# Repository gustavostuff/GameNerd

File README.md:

> **Status:** Active work has shifted to **[Retr01 Nano](nano/README.md)**, a smaller, simpler sibling meant to ship first. The full Retr01 design below is paused for now. It remains the long-term target once Nano is solid.

Retr01 is an MCU-assisted 8-bit system, complemented by a software toolchain. The software consists of 3 different (WIP) packages:

- **Retr01 Studio**: the game editor. Draw maps, tiles, and sprites, then hit **Play** to try your game (uses the emulator render code).
- **Retr01 Emu**: the standalone game player. Runs a cartridge image on your computer. Studio Play uses this same engine.
- **Retr01 Sim**: the board simulator. Shows the ICs and wiring of the motherboard so we can bring up the real design before hardware.

This is the overall hardware roadmap:

- **Retr01-A and Retr01-C** (Arcade and Console): One THT board for both shells. Same **23-IC** core, [**36-pin cart**](docs/cart.md), **RGBS + composite**, 5 V barrel. Arcade microswitch headers **and** PCB footprints for **2x Switchcraft 35RAPC** TRS ([`docs/controllers.md`](docs/controllers.md)).
- **Retr01-H (stage 2)**: Handheld. SMD, battery, LCD + driver, contact pads. Same software contract. It will also include 3.5mm ports for controllers and possibly one more for mono audio + composite.

## Apps

`./build-all` builds Release **Studio**, **Emu**, **Sim**, **Nano Studio**, **Nano Emu**, and **Nano Sim** into `bin/`. `./studio`, `./emu`, and `./sim` (at root) run the full Retr01 binaries. `./unit-tests` runs their test suites.

**Retr01 Nano** (design + apps under [`nano/`](nano/README.md)): `./nano_studio` (optional project path), `./nano_emu [cart.r01nano]`, and `./nano_sim [cart.r01nano]`.

## Main specs

| Aspect | Description |
|--|--|
| CPU | W65C02S @ **8 MHz** |
| Playfield | **128 x 120** of logical resolution (**16 x 15** tiles), board **2x** to **256 x 240** RGBS field |
| Art | **8 x 8** tiles, **2 bpp**, **64** master colors on-board Color PROM IC |
| Worlds | up to **8** worlds x **48** screens each (384-screen "real state"). All within a 512KB cartridge |
| Scroll | **2 x 2** live nametable window + **true second BG** (SNES-like parallax via color-0 show-through) |
| Sprites | **128** OAM entries, **16** per scanline |
| VRAM / RAM | **32 KB** interleaved VRAM + **32 KB** system RAM |

In cartridge, same **32 KB PRG** as classic NES NROM games (Exitebike, Balloon Fight, Ice Climbers) but it buys far more game: **4.5x** more CPU cycles per frame at **8 MHz**, **32 KB** system RAM (not 2 KB). Scroll, sprite line fill and world map streaming are hardware jobs, so PRG stays game logic, not VBlank nametable tricks. A structured **BG0** far plane scrolls under BG1 (color **0** windows) for real dual-layer parallax, not a mapper hack. See [`docs/selling_points.md`](docs/selling_points.md).

## Screenshots

Peek at Retr01 Studio:

Emulator:

Sim:

Main PCB - preliminary design, not tested:

Cart PCB - preliminary design, not tested:

## Where to go next

- [`docs/graphics.md`](docs/graphics.md): VRAM, BG0/BG1, sprites, palettes, graphics ports
- [`docs/selling_points.md`](docs/selling_points.md): NES vs Retr01, including **SNES-like parallax (BG0)**
- [`docs/memory.md`](docs/memory.md): chips, cart layout, read/write timing
- [`docs/hardware.md`](docs/hardware.md): IC BOM, block diagram, bring-up (chips only)
- [`docs/cart.md`](docs/cart.md): cartridge pinout, form factor, USB-C flasher
- [`docs/controllers.md`](docs/controllers.md): Retr01-A arcade vs Retr01-C pad protocol
- [`docs/lightgun.md`](docs/lightgun.md): CRT light gun accessory (roadmap)
- [`docs/passive_rf_etc.md`](docs/passive_rf_etc.md): passives, ports, stackup / RF
- [`docs/sound.md`](docs/sound.md): APU and bytecode
- [`hw/`](hw/): part list + [`hw/md/`](hw/md/) chip notes. Live KiCad: [`hw/kicad/`](hw/kicad/README.md)

Built for people who want to *make* 8-bit games, not only play them.

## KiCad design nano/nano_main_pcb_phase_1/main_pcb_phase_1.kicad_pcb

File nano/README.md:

# Retr01 Nano

**The smallest, cutest, simplest cartridge-based dual gaming system (arcade + console).**

**Status: Phase 1 bring-up next.** Host Studio / Emu / Sim already run a MAP-only picture path. Console silicon starts with a bare RGBS lab setup (below). Later phases grow toward the full Nano form already sketched in [`docs/`](docs/).

Retr01 Nano is a **spiritual child** of [Retr01](../README.md): same 128-wide arcade language, far less hardware. One **ATmega1284P** runs a **fixed, open console firmware**. Games live on a **tiny dual-sided cartridge** (SPI EEPROM + save EEPROM). There is **no 6502** and **no external video ASIC**.

## Roadmap (phases)

We are starting at **Phase 1** (not phase 0). Later phases add the rest of the product. The tables and docs below describe that **final form**. Phase 1 is only the smallest path that proves RGBS on a real CRT.

### How we bring up hardware

We grow the console **one phase at a time** instead of assembling the full board and then sorting out every fault at once. Each phase documents, models, builds, and tests a bounded slice of hardware. If something fails, the cause is almost certainly in what that phase added.

Within each phase:

1. **Document** the hardware and how it should behave (pin map, nets, timing, expected picture / signals). Much of the final BOM is already planned in [`docs/`](docs/), so this step often refines known parts rather than inventing them.
2. **Model** that slice in SKiDL directly, or first in **Nano Sim** and then in SKiDL (see [`schematic_generator/`](schematic_generator/), including `generate_phase1.py`).
3. **Import** the updated / expanded netlist into KiCad. Generate or refresh a realistic BOM there (cross-check against the docs from step 1).
4. **Buy** only the new parts for that phase, wire them onto the current protoboard, and **test** on the bench (flash, probe, CRT).

That loop keeps documentation, design, implementation, and validation aligned. Full-board bring-up is deferred until the slices already work.

### Phase 1 (now): RGBS video lab

Goal: prove the video pipeline on a real CRT. Firmware holds a small pattern in ATmega RAM (black backdrop plus a few randomly placed colored squares from the **8** board FG colors), composes **128x96 @ ~60 Hz**, and drives **RGBS** at **256x192** via **2x**. No cart load yet.

| Need | Role |
|------|------|
| ATmega1284P **PDIP-40** | MCU. Flash open firmware. Hold the RAM pattern |
| External **20 MHz** crystal (+ load caps) | Solid clock from Phase 1 (same preferred rate as the final board) |
| 1 or 2 protoboards | Wire MCU + crystal + resistor DAC + power only |
| USBasp | Flash the ATmega (ISP / `J_ISP` pinout) |
| DC barrel jack to screw-terminal adapter | Plug Mean Well **+5V** into the female jack. Screw jumpers on **+** / **-** into the proto rails |
| Resistors | Build analog **R / G / B / CSYNC** (RGBS) per [`docs/pinmap.md`](docs/pinmap.md) |

**Out of scope for Phase 1:** player input, audio, cart flash, save EEPROM, AD725 / composite, sprites, Studio cart load on the MCU.

**Success:** flash via USBasp, run a minimal scanline kernel, see a stable **128x96** (shown **2x**) picture of random colored squares on black over RGBS on the CRT.

### Later phases (final form)

Build toward the full Nano already planned in the docs:

| Area | Final form (docs) |
|------|-------------------|
| Worlds / screens | Up to **8** worlds, **16** present screens/world, **16x16** virtual grid |
| Picture | **1 bpp** tiles, **8** board FG colors, black backdrop, **128x96** logical, **256x192** RGBS via **2x** |
| Motion | Instant screen switch only (no scrolling) |
| Sprites | Soft display sprites (rebuilt after MAP base). Caps TBD in [`docs/graphics.md`](docs/graphics.md) |
| Players | **2P** pad bytes (Retr01 spirit) |
| Audio | **2 PWM** channels (music pulse + SFX), resistor-mixed |
| Cart | **25LC1024** (128 KB game) + **24C64** save, cute **8+8** edge |
| Firmware | Fixed open image on the 1284. Games are cart data |

| | Retr01 (full) | Retr01 Nano (final form) |
|--|---------------|--------------------------|
| CPU / host | 6502 + MCUs | Single ATmega1284P @ 20 MHz (preferred) |
| Storage | Large cart flash + 24C64 | **Cute cart:** **25LC1024** (128 KB, DIP-8) + **24C64** (DIP-8) |
| Firmware | Cart PRG + MCU assists | **Fixed open** 1284 firmware (community-flashable) |
| Video | Multi-layer tile / sprite pipeline | 1 bpp tiles, attr FG color, soft sprites (later) |
| Worlds | Up to 8, rich MAP | Up to **8** worlds, **16** screens/world, **16x16** screen grid |
| Resolution (target) | 128x120 logical playfield | **128x96** logical, **256x192** RGBS via **2x** |
| Motion | Pixel scroll + streaming | **Instant screen switch only** |
| Players | 2P arcade GPIO | **2P** same pad-byte spirit |
| Audio | Multi-channel APU path | **2 PWM channels** (music pulse + SFX), resistor-mixed |

Primary product goal: a **minimal, stable 60 Hz** board with the smallest carts we can get away with, still feeling like Retr01. See [`docs/video.md`](docs/video.md) and [`docs/overview.md`](docs/overview.md).

## Host apps (Studio / Emu / Sim)

For now, **Nano Studio**, **Nano Emu**, and **Nano Sim** are **independent** trees under [`apps/`](apps/) (and root launchers). They may start as copies of the full Retr01 tools and diverge freely.

Later they are intended to **share common code** with the full Studio / Emu / Sim apps (shared libraries or extracted modules) instead of remaining permanent forks. Until that merge, prefer fixing Nano behavior in the Nano tree and keep full apps unchanged unless a change is deliberately shared.

**Apps:** [`apps/studio/`](apps/studio/) is Nano Studio. [`apps/emu/`](apps/emu/) is Nano Emu (MAP preview). [`apps/sim/`](apps/sim/) is the IC/netlist board. See [`apps/README.md`](apps/README.md).

| Runner | Picture | Host audio overlay |
|--------|---------|--------------------|
| Nano Studio Play | MAP preview (export + emu) | Yes |
| `./nano_emu` | MAP preview | No |
| `./nano_sim` | Soft compose MAP | No |

Host runners are **ahead of Phase 1 silicon**. They already compose MAP tiles from a cart image. Phase 1 MCU firmware does not load carts yet. It only proves RGBS from patterns in ATmega RAM.

## Docs

| Doc | Topic |
|-----|--------|
| [`docs/overview.md`](docs/overview.md) | Goals, cuts, roadmap |
| [`docs/graphics.md`](docs/graphics.md) | Worlds, screens, attr byte, MAP compose |
| [`docs/video.md`](docs/video.md) | RGBS, 2x to 256x192, line buffers, VBlank loads |
| [`docs/memory_and_software.md`](docs/memory_and_software.md) | MCU vs cart budgets, open firmware, SDK |
| [`docs/cache_architecture.md`](docs/cache_architecture.md) | How 16 KB SRAM caches cart MAP/CHR without filling to the brim |
| [`docs/sound.md`](docs/sound.md) | 2-channel music + SFX PWM |
| [`docs/cart_format.md`](docs/cart_format.md) | `.r01proj` + `.r01nano` / 128 KB flash layout |
| [`docs/hardware.md`](docs/hardware.md) | Mobo + cute cart connector, BOM sketch |
| [`docs/pinmap.md`](docs/pinmap.md) | MCU PORT / PDIP-40 map, headers, cart edge |
| [`schematic_generator/`](schematic_generator/) | SKiDL. Phase 1: `generate_phase1.py` -> `nano_phase1.net`. Full: `nano_mobo.net` + `nano_cart.net` |

From the repo root:

| Command | Role |
|---------|------|
| `./nano_studio [project.r01proj]` | Nano Studio (`bin/nano_studio` from `./build-all`) |
| `./nano_emu [cart.r01nano]` | Nano Emu MAP preview (`bin/nano_emu`) |
| `./nano_sim [cart.r01nano]` | Nano Sim: IC/netlist board UI (islands + DIPs + SCR), not a fullscreen emu |

Source concept notes also live in `temp/Retr01_Nano_Spec.md`. Where this tree disagrees, **these docs win**.

## Non-goals (final product v1)

- Compatibility with full Retr01 `.retr01` cart images or 36-pin edge
- Composite / NTSC encoder chips on the Phase 1 lab (AD725 remains a later board option)
- Hardware sprites, BG0, any screen scrolling
- Full Retr01 Sim netlist reuse

**Authoring:** Nano Studio exports `.r01nano` today (MAP + CHR). Console firmware / C SDK on the 1284 start with Phase 1 RGBS bring-up. Direction: open **C** firmware/SDK plus a tiny assembly video kernel. Game data lands on the SPI cart in later phases.

## Screenshots

## License / ownership

Same project umbrella as Retr01. Console firmware is intended to stay **open** for the community. See the parent repo for licensing when published.

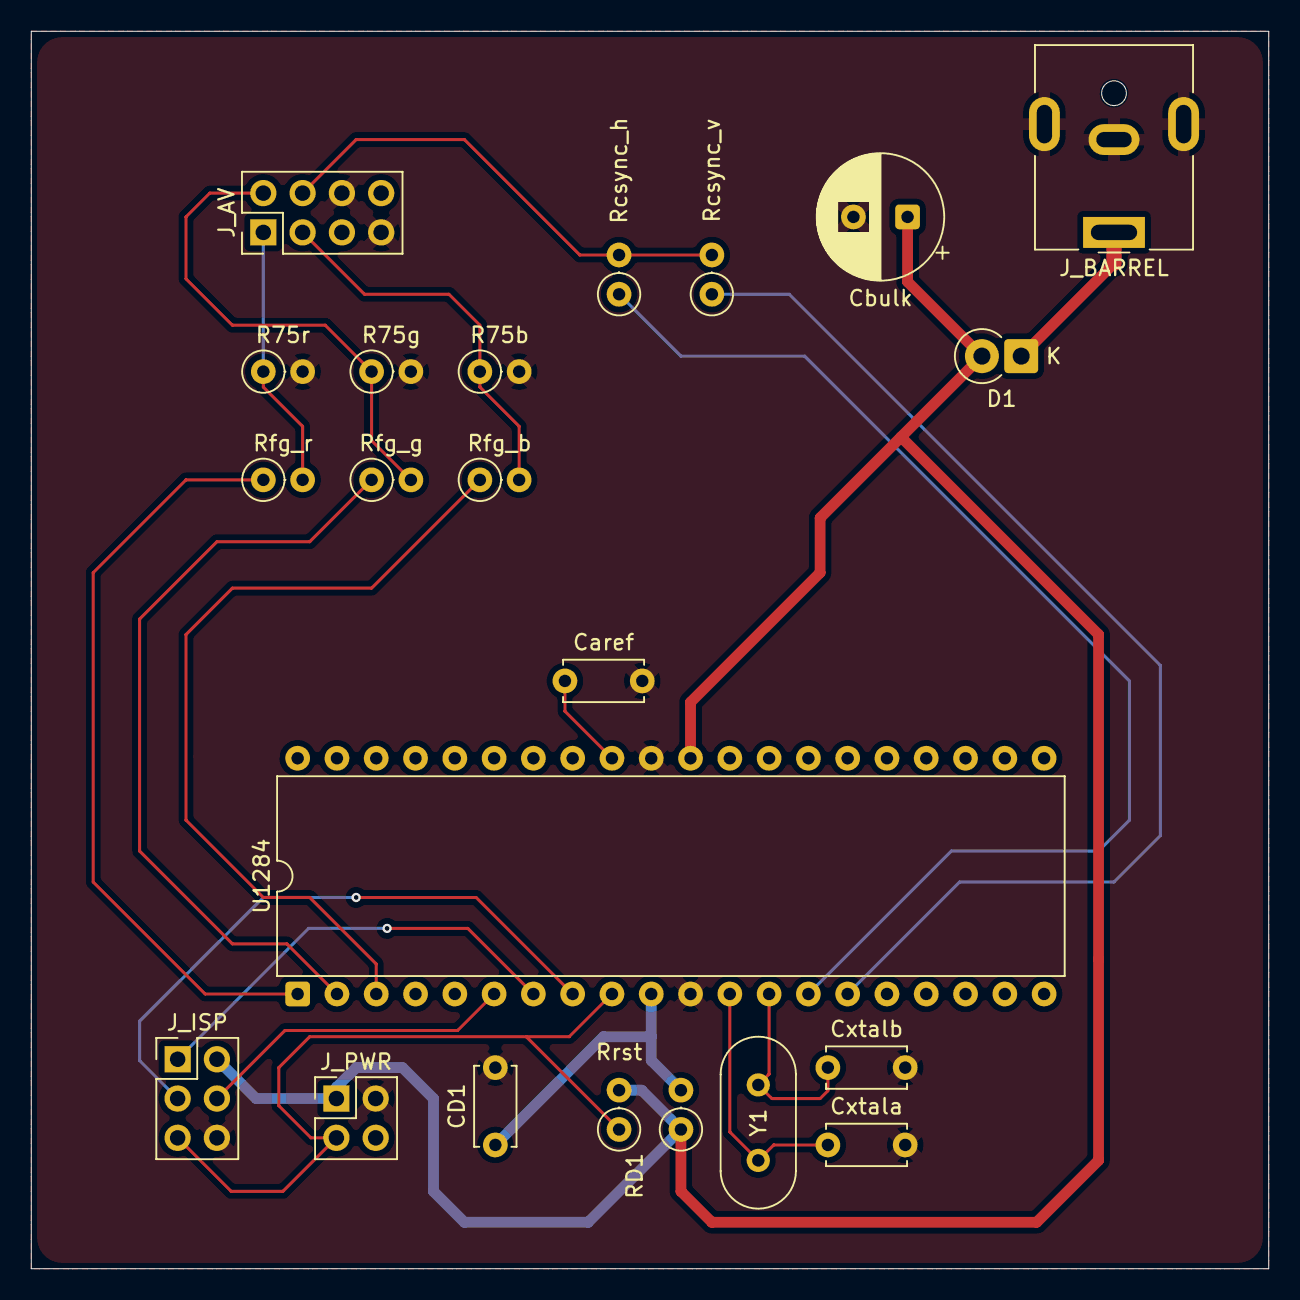
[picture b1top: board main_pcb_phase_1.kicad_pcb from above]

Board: 2 copper layers, 80.0 x 80.0 mm, 22 parts (0 on the bottom side), 20 nets.

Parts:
CD1: 100nF; C_Disc_D5.0mm_W2.5mm_P5.00mm
Caref: 100nF; C_Disc_D5.0mm_W2.5mm_P5.00mm
Cbulk: 220uF; CP_Radial_D8.0mm_P3.50mm
Cxtala: 22pF; C_Disc_D5.0mm_W2.5mm_P5.00mm
Cxtalb: 22pF; C_Disc_D5.0mm_W2.5mm_P5.00mm
D1: SCHOTTKY; D_DO-41_SOD81_P2.54mm_Vertical_CathodeUp
J_AV: J_AV; PinHeader_2x04_P2.54mm_Vertical
J_BARREL: BARREL_5V; BarrelJack_CUI_PJ-063AH_Horizontal
J_ISP: J_ISP; PinHeader_2x03_P2.54mm_Vertical
J_PWR: J_PWR; PinHeader_2x02_P2.54mm_Vertical
R75b, R75g, R75r: 75R; R_Axial_DIN0207_L6.3mm_D2.5mm_P2.54mm_Vertical
RD1: 0R; R_Axial_DIN0207_L6.3mm_D2.5mm_P2.54mm_Vertical
Rcsync_h: 1k; R_Axial_DIN0207_L6.3mm_D2.5mm_P2.54mm_Vertical
Rcsync_v: 1k; R_Axial_DIN0207_L6.3mm_D2.5mm_P2.54mm_Vertical
Rfg_b: 470R; R_Axial_DIN0207_L6.3mm_D2.5mm_P2.54mm_Vertical
Rfg_g: 470R; R_Axial_DIN0207_L6.3mm_D2.5mm_P2.54mm_Vertical
Rfg_r: 470R; R_Axial_DIN0207_L6.3mm_D2.5mm_P2.54mm_Vertical
Rrst: 10k; R_Axial_DIN0207_L6.3mm_D2.5mm_P2.54mm_Vertical
U1284: ATmega1284P; DIP-40_W15.24mm
Y1: XTAL_20M; Crystal_HC49-U_Vertical

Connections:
+5V: Cbulk.1, D1.2, J_ISP.2, J_PWR.1, RD1.1, Rrst.2, U1284.30
+5V_U1284: CD1.1, RD1.2, U1284.10
AREF: Caref.1, U1284.32
B: J_AV.3, R75b.1, Rfg_b.2
CSYNC: J_AV.4, Rcsync_h.2, Rcsync_v.2
FG0: Rfg_r.1, U1284.1
FG1: Rfg_g.1, U1284.2
FG2: Rfg_b.1, U1284.3
G: J_AV.2, R75g.1, Rfg_g.2
GND: CD1.2, Caref.2, Cbulk.2, Cxtala.2, Cxtalb.2, J_AV.6, J_AV.7, J_BARREL.2, J_BARREL.MP, J_ISP.6, J_PWR.2, R75b.2, R75g.2, R75r.2, U1284.11, U1284.31
HSYNC: Rcsync_h.1, U1284.14
R: J_AV.1, R75r.1, Rfg_r.2
RESET#: J_ISP.5, J_PWR.3, Rrst.1, U1284.9
SPI_MISO: J_ISP.1, U1284.7
SPI_MOSI: J_ISP.4, U1284.6
SPI_SCK: J_ISP.3, U1284.8
VIN_RAW: D1.1, J_BARREL.1
VSYNC: Rcsync_v.1, U1284.15
XTAL1: Cxtalb.1, U1284.13, Y1.2
XTAL2: Cxtala.1, U1284.12, Y1.1

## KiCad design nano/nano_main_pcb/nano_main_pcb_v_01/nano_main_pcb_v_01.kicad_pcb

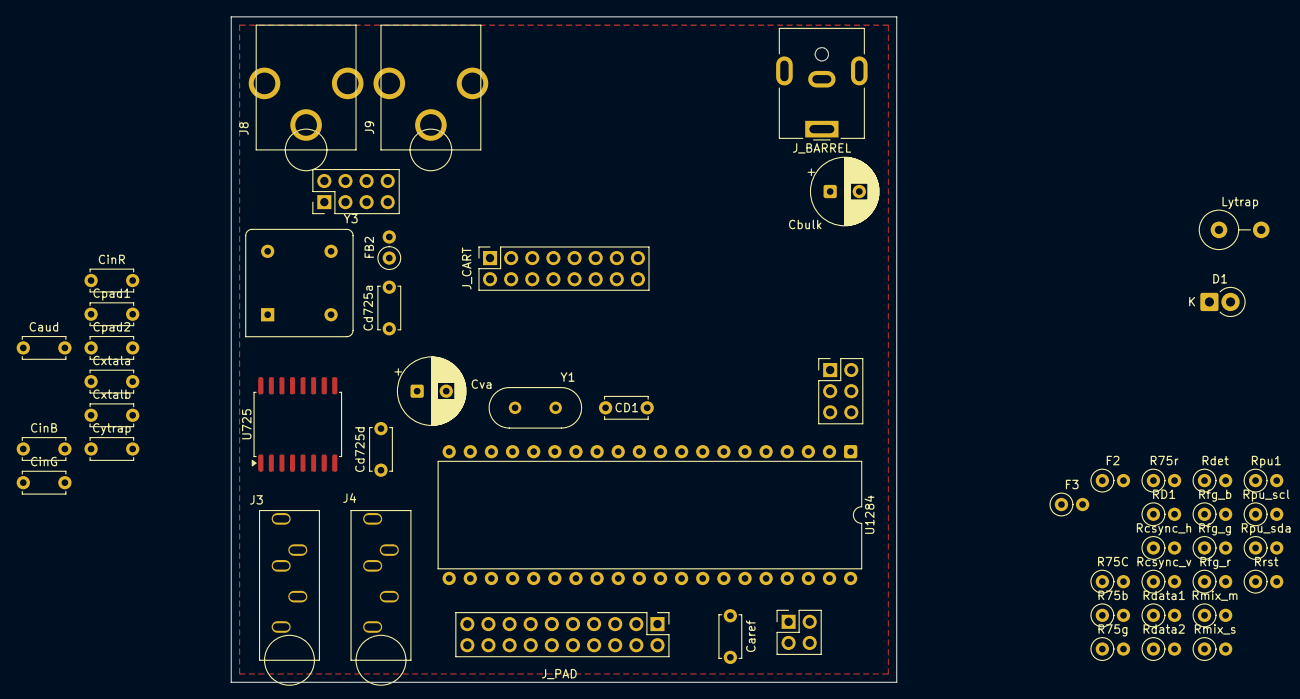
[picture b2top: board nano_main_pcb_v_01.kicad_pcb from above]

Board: 2 copper layers, 80.0 x 80.0 mm, 53 parts (0 on the bottom side), 59 nets, no tracks yet.

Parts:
CD1: 100nF; C_Disc_D5.0mm_W2.5mm_P5.00mm
Caref: 100nF; C_Disc_D5.0mm_W2.5mm_P5.00mm
Caud: 10uF; C_Disc_D5.0mm_W2.5mm_P5.00mm
Cbulk: 220uF; CP_Radial_D8.0mm_P3.50mm
Cd725a, Cd725d: 100nF; C_Disc_D5.0mm_W2.5mm_P5.00mm
CinB: 100nF; C_Disc_D5.0mm_W2.5mm_P5.00mm
CinG: 100nF; C_Disc_D5.0mm_W2.5mm_P5.00mm
CinR: 100nF; C_Disc_D5.0mm_W2.5mm_P5.00mm
Cpad1, Cpad2: 100nF; C_Disc_D5.0mm_W2.5mm_P5.00mm
Cva: 10uF; CP_Radial_D8.0mm_P3.50mm
Cxtala: 22pF; C_Disc_D5.0mm_W2.5mm_P5.00mm
Cxtalb: 22pF; C_Disc_D5.0mm_W2.5mm_P5.00mm
Cytrap: 100nF; C_Disc_D5.0mm_W2.5mm_P5.00mm
D1: SCHOTTKY; D_DO-41_SOD81_P2.54mm_Vertical_CathodeUp
F2, F3: PPTC; R_Axial_DIN0207_L6.3mm_D2.5mm_P2.54mm_Vertical
FB2: FERRITE; R_Axial_DIN0207_L6.3mm_D2.5mm_P2.54mm_Vertical
J3: TRS_P1; Jack_3.5mm_Switchcraft_35RAPC2BVN4_Vertical
J4: TRS_P2; Jack_3.5mm_Switchcraft_35RAPC2BVN4_Vertical
J8: AUDIO_OUT; CUI_RCJ-01x_Vertical
J9: COMPOSITE; CUI_RCJ-01x_Vertical
J_AV: J_AV; PinHeader_2x04_P2.54mm_Vertical
J_BARREL: BARREL_5V; BarrelJack_CUI_PJ-063AH_Horizontal
J_CART: CART_SOCKET_16; PinSocket_2x08_P2.54mm_Vertical
J_ISP: J_ISP; PinHeader_2x03_P2.54mm_Vertical
J_PAD: J_PAD; PinHeader_2x10_P2.54mm_Vertical
J_PWR: J_PWR; PinHeader_2x02_P2.54mm_Vertical
Lytrap: L_YTRAP; L_Axial_L11.0mm_D4.5mm_P5.08mm_Vertical_Fastron_MECC
R75C, R75b, R75g, R75r: 75R; R_Axial_DIN0207_L6.3mm_D2.5mm_P2.54mm_Vertical
RD1: 0R; R_Axial_DIN0207_L6.3mm_D2.5mm_P2.54mm_Vertical
Rcsync_h: 1k; R_Axial_DIN0207_L6.3mm_D2.5mm_P2.54mm_Vertical
Rcsync_v: 1k; R_Axial_DIN0207_L6.3mm_D2.5mm_P2.54mm_Vertical
Rdata1, Rdata2: 47R; R_Axial_DIN0207_L6.3mm_D2.5mm_P2.54mm_Vertical
Rdet: 10k; R_Axial_DIN0207_L6.3mm_D2.5mm_P2.54mm_Vertical
Rfg_b: 470R; R_Axial_DIN0207_L6.3mm_D2.5mm_P2.54mm_Vertical
Rfg_g: 470R; R_Axial_DIN0207_L6.3mm_D2.5mm_P2.54mm_Vertical
Rfg_r: 470R; R_Axial_DIN0207_L6.3mm_D2.5mm_P2.54mm_Vertical
Rmix_m: 1k; R_Axial_DIN0207_L6.3mm_D2.5mm_P2.54mm_Vertical
Rmix_s: 1k; R_Axial_DIN0207_L6.3mm_D2.5mm_P2.54mm_Vertical
Rpu1: 4.7k; R_Axial_DIN0207_L6.3mm_D2.5mm_P2.54mm_Vertical
Rpu_scl: 4.7k; R_Axial_DIN0207_L6.3mm_D2.5mm_P2.54mm_Vertical
Rpu_sda: 4.7k; R_Axial_DIN0207_L6.3mm_D2.5mm_P2.54mm_Vertical
Rrst: 10k; R_Axial_DIN0207_L6.3mm_D2.5mm_P2.54mm_Vertical
U725: AD725; SOIC-16W_7.5x10.3mm_P1.27mm
U1284: ATmega1284P; DIP-40_W15.24mm
Y1: XTAL_20M; Crystal_HC49-U_Vertical
Y3: OSC_4FSC; Oscillator_DIP-8

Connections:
+5V: Cbulk.1, D1.2, F2.1, F3.1, FB2.1, J_CART.2, J_CART.10, J_ISP.2, J_PWR.1, RD1.1, Rdet.2, Rpu1.1, Rpu_scl.2, Rpu_sda.2, Rrst.2, U725.1, U725.5, U725.15, U1284.30, Y3.1, Y3.8
+5V_ANALOG: Cd725a.1, Cd725d.1, Cva.1, FB2.2, U725.4, U725.14
+5V_U1284: CD1.1, RD1.2, U1284.10
AD725_BIN: CinB.2, U725.8
AD725_GIN: CinG.2, U725.7
AD725_RIN: CinR.2, U725.6
AREF: Caref.1, U1284.32
AUD: Caud.2, J8.1, J_AV.5
AUD_MIX: Caud.1, Rmix_m.2, Rmix_s.2
B: CinB.1, J_AV.3, R75b.1, Rfg_b.2
CART_DET#: J_CART.16, Rdet.1, U1284.4
COMPOSITE_OUT: J9.1, R75C.2
COMP_RAW: R75C.1, U725.10
CSYNC: J_AV.4, Rcsync_h.2, Rcsync_v.2, U725.16
FG0: Rfg_r.1, U1284.1
FG1: Rfg_g.1, U1284.2
FG2: Rfg_b.1, U1284.3
FSC4: U725.3, Y3.5
G: CinG.1, J_AV.2, R75g.1, Rfg_g.2
GND: CD1.2, Caref.2, Cbulk.2, Cd725a.2, Cd725d.2, Cpad1.2, Cpad2.2, Cva.2, Cxtala.2, Cxtalb.2, Cytrap.2, J3.1, J4.1, J8.2, J9.2, J_BARREL.2, J_BARREL.MP, J_CART.1, J_CART.9, J_ISP.6, J_PAD.17, J_PAD.18, J_PWR.2, U725.2, U725.13, U1284.11, U1284.31, Y3.4
HSYNC: Rcsync_h.1, U1284.14
I2C_SCL: J_CART.8, Rpu_scl.1, U1284.22
I2C_SDA: J_CART.7, J_CART.15, Rpu_sda.1, U1284.23
P1_D0: J_PAD.1, U1284.40
P1_D1: J_PAD.3, U1284.39
P1_D2: J_PAD.5, U1284.38
P1_D3: J_PAD.7, U1284.37
P1_D4: J_PAD.9, U1284.36
P1_D5: J_PAD.11, U1284.35
P1_D6: J_PAD.13, U1284.34
P1_D7: J_PAD.15, U1284.33
P2_D0: J_PAD.2, U1284.24
P2_D1: J_PAD.4, U1284.25
P2_D2: J_PAD.6, U1284.26
P2_D3: J_PAD.8, U1284.27
P2_D4: J_PAD.10, U1284.28
P2_D5: J_PAD.12, U1284.29
P2_D6: J_PAD.14, U1284.20
P2_D7: J_PAD.16, U1284.21
PAD_DATA: Rdata1.1, Rdata2.1, Rpu1.2, U1284.16
PAD_DATA_P1: J3.2, Rdata1.2
PAD_DATA_P2: J4.2, Rdata2.2
PAD_VCC_P1: Cpad1.1, F2.2, J3.4
PAD_VCC_P2: Cpad2.1, F3.2, J4.4
PWM_MUSIC: Rmix_m.1, U1284.19
PWM_SFX: Rmix_s.1, U1284.18
R: CinR.1, J_AV.1, R75r.1, Rfg_r.2
RESET#: J_ISP.5, J_PWR.3, Rrst.1, U1284.9
SPI_MISO: J_CART.6, J_CART.14, J_ISP.1, U1284.7
SPI_MOSI: J_CART.5, J_CART.13, J_ISP.4, U1284.6
SPI_SCK: J_CART.4, J_CART.12, J_ISP.3, U1284.8
SPI_SS#: J_CART.3, J_CART.11, U1284.5
VGND: J_AV.7, R75b.2, R75g.2, R75r.2
VIN_RAW: D1.1, J_BARREL.1
VSYNC: Rcsync_v.1, U1284.15
XTAL1: Cxtalb.1, U1284.13, Y1.2
XTAL2: Cxtala.1, U1284.12, Y1.1
YTRAP: Lytrap.1, U725.12
YTRAP_MID: Cytrap.1, Lytrap.2

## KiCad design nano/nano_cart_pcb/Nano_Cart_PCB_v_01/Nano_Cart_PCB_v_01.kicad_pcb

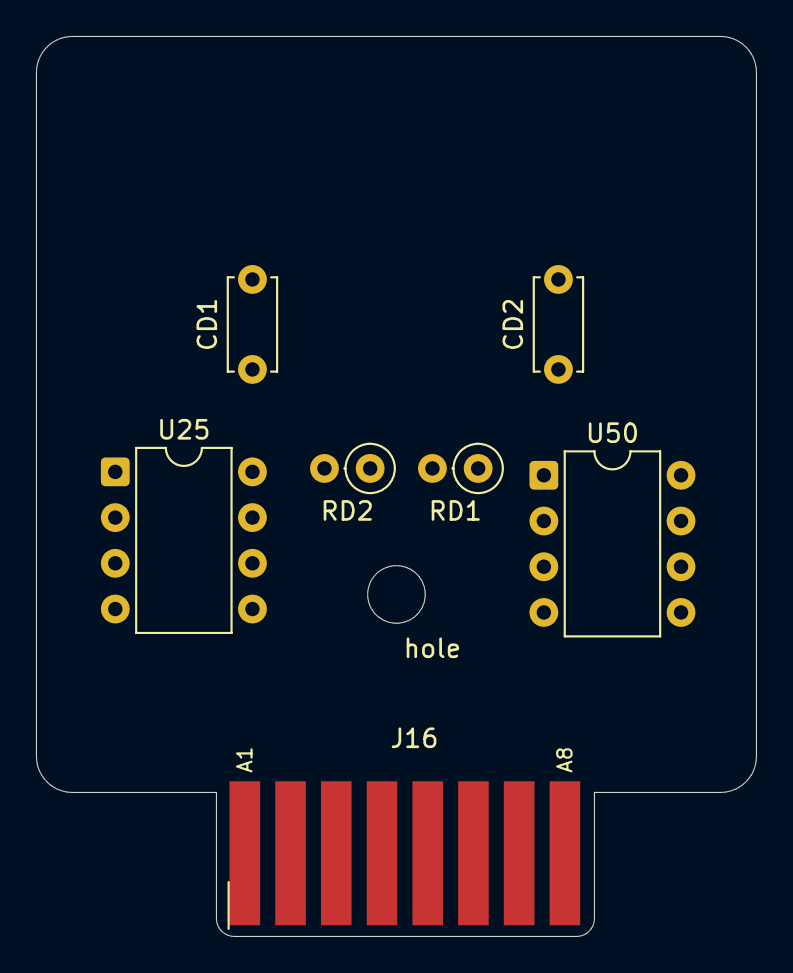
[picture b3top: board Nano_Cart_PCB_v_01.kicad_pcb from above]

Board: 2 copper layers, 40.0 x 50.0 mm, 8 parts (0 on the bottom side), 10 nets, no tracks yet.

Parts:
CD1, CD2: 100nF; C_Disc_D5.0mm_W2.5mm_P5.00mm
J16: CART_EDGE_16; Cart_Edge_2x8_P2.54mm
RD1, RD2: 0R; R_Axial_DIN0207_L6.3mm_D2.5mm_P2.54mm_Vertical
U25: 25LC1024; DIP-8_W7.62mm
U50: 24C64; DIP-8_W7.62mm
hole: MountingHole_3.2mm_M3

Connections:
+5V: J16.2, J16.10, RD1.1, RD2.1, U25.3, U25.7
+5V_U25: CD1.1, RD1.2, U25.8
+5V_U50: CD2.1, RD2.2, U50.8
GND: CD1.2, CD2.2, J16.1, J16.9, U25.4, U50.1, U50.2, U50.3, U50.4, U50.7
I2C_SCL: J16.8, U50.6
I2C_SDA: J16.7, J16.15, U50.5
SPI_MISO: J16.6, J16.14, U25.2
SPI_MOSI: J16.5, J16.13, U25.5
SPI_SCK: J16.4, J16.12, U25.6
SPI_SS#: J16.3, J16.11, U25.1

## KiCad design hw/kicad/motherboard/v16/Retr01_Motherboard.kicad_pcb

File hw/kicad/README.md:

# Retr01 KiCad projects

Single home for PCB / project files and the custom footprint library.

**Netlists** still come from [`app/schematic_generator/`](../../app/schematic_generator/) (`python generate.py`). Import into the live projects below. Quilter Circuit Comprehension notes: [`docs/passive_rf_etc.md`](../../docs/passive_rf_etc.md) (power nets + bypass caps).

## Layout

| Path | Role |
|------|------|
| **[`motherboard/`](motherboard/)** | **Live** motherboard project. Open `Retr01_Motherboard.kicad_pro` |
| **[`cartridge/`](cartridge/)** | **Live** cartridge project. Open `Retr01_Cartridge.kicad_pro` |
| **[`Retr01_Lib.pretty/`](Retr01_Lib.pretty/)** | Custom footprints (TRS, RCA, cart gold fingers). Full Retr01 + **Nano** KiCad projects point here via `fp-lib-table` |
| **[`archive/`](archive/)** | Old boards and Quilter downloads (not the working copy) |

```text
hw/kicad/
+-- Retr01_Lib.pretty/     # authority footprint lib
+-- motherboard/           # live mobo (from former v07)
+-- cartridge/             # live cart
+-- archive/
    +-- motherboard_v01/   # first KiCad project
    +-- snapshots_v02/     # intermediate v02-v07 saves
    +-- quilter/           # Quilter candidate exports
```

## Cartridge gold fingers

Cart netlist `J36` uses `Retr01_Lib:Cart_Edge_2x18_P2.54mm` (pads **1-18** = A / F.Cu, **19-36** = B / B.Cu). Motherboard `J36` stays on the PinSocket stand-in.

**Import / swap in Pcbnew:**

1. Draw `Edge.Cuts` (~**55 x 55 mm**, thickness **1.6 mm**, **4-layer** F/GND/GND/B).
2. `File` -> `Import` -> `Netlist` -> `app/schematic_generator/output/retr01_cart.net` (or Update PCB from schematic if you keep a sch).
3. If an old PinSocket `J36` is still on the board: delete it, then Update PCB so the gold-finger footprint appears.
4. Place `J36` with origin on the insert edge. Pads point into the board (+X in the footprint). Silk **A1** marks side A pin 1.
5. Place U40 / U50 / caps and route.

**Quilter (cart):** Circuit Comprehension checklist is in [`docs/passive_rf_etc.md`](../../docs/passive_rf_etc.md#quilter-circuit-comprehension---cartridge-pcb) (4-layer SIG/GND/GND/SIG, full-board `+5V` on outers, `GND` on inners, stubs pour off, `CD1`/`CD2` only). KiCad: `J36` and `Edge.Cuts` locked; copper zones cover the full outline. After reopen, **Edit -> Fill All Zones**.

Confirm `fp-lib-table` resolves `Retr01_Lib` (already set for `cartridge/`).

SKiDL / schem generator uses the same footprints via a symlink: `app/schematic_generator/library/Retr01_Lib.pretty` -> this folder.

## Archive policy

Do not edit under `archive/` for new layout work. Copy a snapshot into `motherboard/` only if you intentionally revive an old spin. Quilter zips and candidate PCBs stay in `archive/quilter/`.

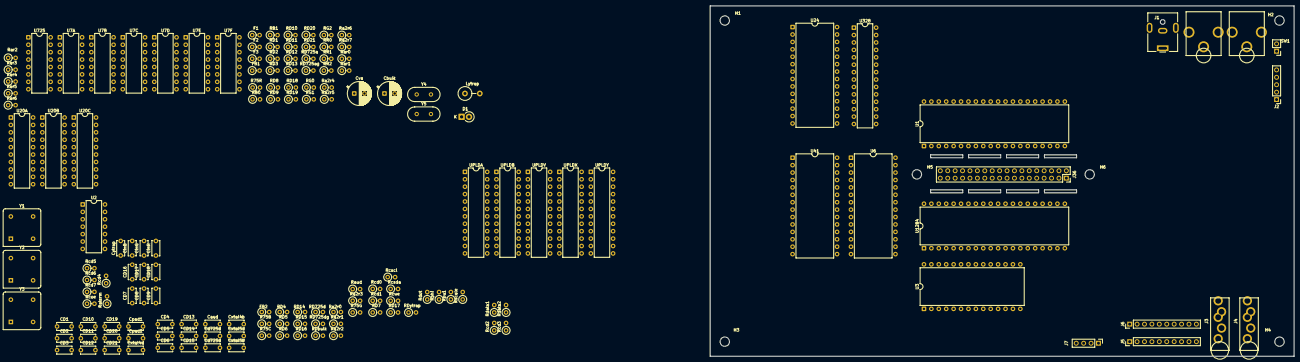
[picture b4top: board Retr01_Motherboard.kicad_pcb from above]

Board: 4 copper layers, 200.0 x 120.0 mm, 162 parts (0 on the bottom side), 214 nets, no tracks yet.

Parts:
CD1, CD2, CD3, CD4, CD5, CD6, CD7, CD8, CD9, CD10, CD11, CD12, CD13, CD14, CD15, CD16, CD17, CD18, CD19, CD20, CD21: 100nF; C_Disc_D5.0mm_W2.5mm_P5.00mm
Caud: 10uF; C_Disc_D5.0mm_W2.5mm_P5.00mm
Cbulk: 220uF; CP_Radial_D8.0mm_P3.50mm
Cd725a, Cd725d: 100nF; C_Disc_D5.0mm_W2.5mm_P5.00mm
CinB: 100nF; C_Disc_D5.0mm_W2.5mm_P5.00mm
CinG: 100nF; C_Disc_D5.0mm_W2.5mm_P5.00mm
CinR: 100nF; C_Disc_D5.0mm_W2.5mm_P5.00mm
Cpad1, Cpad2: 100nF; C_Disc_D5.0mm_W2.5mm_P5.00mm
Cva: 10uF; CP_Radial_D8.0mm_P3.50mm
Cxtal4a, Cxtal4b, Cxtal5a, Cxtal5b: 22pF; C_Disc_D5.0mm_W2.5mm_P5.00mm
Cytrap: 100nF; C_Disc_D5.0mm_W2.5mm_P5.00mm
D1: SCHOTTKY; D_DO-41_SOD81_P2.54mm_Vertical_CathodeUp
F1, F2, F3: PPTC; R_Axial_DIN0207_L6.3mm_D2.5mm_P2.54mm_Vertical
FB1, FB2: FERRITE; R_Axial_DIN0207_L6.3mm_D2.5mm_P2.54mm_Vertical
H1, H2, H3, H4, H5, H6: MountingHole_3.2mm_M3
J1: BARREL_5V; BarrelJack_CUI_PJ-063AH_Horizontal
J2: RGBS_HDR; PinHeader_1x05_P2.54mm_Vertical
J3: TRS_P1; Jack_3.5mm_Switchcraft_35RAPC2BVN4_Vertical
J4: TRS_P2; Jack_3.5mm_Switchcraft_35RAPC2BVN4_Vertical
J5: ARCADE_P1; PinHeader_1x10_P2.54mm_Vertical
J6: ARCADE_P2; PinHeader_1x10_P2.54mm_Vertical
J7: CAB_PWR_RST; PinHeader_1x04_P2.54mm_Vertical
J8: AUDIO_OUT; CUI_RCJ-01x_Vertical
J9: COMPOSITE; CUI_RCJ-01x_Vertical
J36: CART_EDGE_36; PinSocket_2x18_P2.54mm_Vertical
Lytrap: L_YTRAP; L_Axial_L11.0mm_D4.5mm_P5.08mm_Vertical_Fastron_MECC
R75B, R75C, R75G, R75R: 75R; R_Axial_DIN0207_L6.3mm_D2.5mm_P2.54mm_Vertical
RB0: 2k; R_Axial_DIN0207_L6.3mm_D2.5mm_P2.54mm_Vertical
RB1: 1k; R_Axial_DIN0207_L6.3mm_D2.5mm_P2.54mm_Vertical
RD1, RD2, RD3, RD4, RD5, RD6, RD7, RD8, RD9, RD10, RD11, RD12, RD13, RD14, RD15, RD16, RD17, RD18, RD19, RD20, RD21: 0; R_Axial_DIN0207_L6.3mm_D2.5mm_P2.54mm_Vertical
RD725a, RD725ag, RD725d, RD725dg: 0R; R_Axial_DIN0207_L6.3mm_D2.5mm_P2.54mm_Vertical
RDbulk: 0R; R_Axial_DIN0207_L6.3mm_D2.5mm_P2.54mm_Vertical
RDytrap: 0R; R_Axial_DIN0207_L6.3mm_D2.5mm_P2.54mm_Vertical
RG0: 4k; R_Axial_DIN0207_L6.3mm_D2.5mm_P2.54mm_Vertical
RG1: 2k; R_Axial_DIN0207_L6.3mm_D2.5mm_P2.54mm_Vertical
RG2: 1k; R_Axial_DIN0207_L6.3mm_D2.5mm_P2.54mm_Vertical
RR0: 4k; R_Axial_DIN0207_L6.3mm_D2.5mm_P2.54mm_Vertical
RR1: 2k; R_Axial_DIN0207_L6.3mm_D2.5mm_P2.54mm_Vertical
RR2: 1k; R_Axial_DIN0207_L6.3mm_D2.5mm_P2.54mm_Vertical
Ra2r0, Ra2r1, Ra2r2, Ra2r3, Ra2r4, Ra2r5, Ra2r6, Ra2r7: 20k; R_Axial_DIN0207_L6.3mm_D2.5mm_P2.54mm_Vertical
Rar0, Rar1, Rar2, Rar3, Rar4, Rar5, Rar6: 10k; R_Axial_DIN0207_L6.3mm_D2.5mm_P2.54mm_Vertical
Raterm: 20k; R_Axial_DIN0207_L6.3mm_D2.5mm_P2.54mm_Vertical
Raud: 1k; R_Axial_DIN0207_L6.3mm_D2.5mm_P2.54mm_Vertical
Rcd0, Rcd1, Rcd2, Rcd3, Rcd4, Rcd5, Rcd6, Rcd7: 33R; R_Axial_DIN0207_L6.3mm_D2.5mm_P2.54mm_Vertical
Rcoe: 33R; R_Axial_DIN0207_L6.3mm_D2.5mm_P2.54mm_Vertical
Rcscl: 33R; R_Axial_DIN0207_L6.3mm_D2.5mm_P2.54mm_Vertical
Rcsda: 33R; R_Axial_DIN0207_L6.3mm_D2.5mm_P2.54mm_Vertical
Rcwe: 33R; R_Axial_DIN0207_L6.3mm_D2.5mm_P2.54mm_Vertical
Rdata1, Rdata2: 47R; R_Axial_DIN0207_L6.3mm_D2.5mm_P2.54mm_Vertical
Rdot: 33R; R_Axial_DIN0207_L6.3mm_D2.5mm_P2.54mm_Vertical
Rphi: 33R; R_Axial_DIN0207_L6.3mm_D2.5mm_P2.54mm_Vertical
Rpu1: 4.7k; R_Axial_DIN0207_L6.3mm_D2.5mm_P2.54mm_Vertical
Rscale: 10k; R_Axial_DIN0207_L6.3mm_D2.5mm_P2.54mm_Vertical
SW1: SCALE_SW; PinHeader_1x02_P2.54mm_Vertical
U1: W65C02S; DIP-40_W15.24mm
U2: SN74HC14; DIP-14_W7.62mm
U3, U6, U41: AS6C62256; DIP-28_W15.24mm
U7A, U7B, U7C, U7D, U7E, U7F: SN74HC157; DIP-16_W7.62mm
U20A, U20B, U20C: SN74HC245; DIP-20_W7.62mm
U24: AT27C256R; DIP-28_W15.24mm
U328: ATmega328P; DIP-28_W7.62mm
U725: AD725; DIP-16_W7.62mm
U1284: ATmega1284P; DIP-40_W15.24mm
UPLDA: ATF22V10; DIP-24_W7.62mm
UPLDB: ATF22V10; DIP-24_W7.62mm
UPLDV: ATF22V10; DIP-24_W7.62mm
UPLDX: ATF22V10; DIP-24_W7.62mm
UPLDY: ATF22V10; DIP-24_W7.62mm
Y1: OSC8M; Oscillator_DIP-8
Y2: OSC_DOT; Oscillator_DIP-8
Y3: OSC_4FSC; Oscillator_DIP-8
Y4: XTAL_20M; Crystal_HC49-U_Vertical
Y5: XTAL_16M; Crystal_HC49-U_Vertical

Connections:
+5V: F2.1, F3.1, FB2.1, J7.1, J36.2, J36.20, RD1.2, RD2.2, RD3.2, RD4.2, RD5.2, RD6.2, RD8.2, RD9.2, RD10.2, RD11.2, RD12.2, RD13.2, RD14.2, RD15.2, RD16.2, RD17.2, RD18.2, RD19.2, RD20.2, RD21.2, RDbulk.2, Rpu1.1, SW1.2, U2.14, U725.1, U725.5, U725.15, Y1.1, Y1.8, Y2.1, Y2.8, Y3.1, Y3.8
+5V_ANALOG: Cva.1, FB2.2, RD7.2, RD725a.2, RD725d.2
+5V_BULK: Cbulk.1, FB1.2, RDbulk.1
+5V_U1: CD1.1, RD1.1, U1.8
+5V_U3: CD2.1, RD2.1, U3.28
+5V_U6: CD5.1, RD5.1, U6.28
+5V_U7A: CD13.1, RD13.1, U7A.16
+5V_U7B: CD14.1, RD14.1, U7B.16
+5V_U7C: CD15.1, RD15.1, U7C.16
+5V_U7D: CD16.1, RD16.1, U7D.16
+5V_U7E: CD17.1, RD17.1, U7E.16
+5V_U7F: CD18.1, RD18.1, U7F.16
+5V_U20A: CD19.1, RD19.1, U20A.20
+5V_U20B: CD20.1, RD20.1, U20B.20
+5V_U20C: CD21.1, RD21.1, U20C.20
+5V_U24: CD7.1, RD7.1, U24.28
+5V_U41: CD6.1, RD6.1, U41.28
+5V_U328: CD4.1, RD4.1, U328.7
+5V_U725_APOS: Cd725a.1, RD725a.1, U725.4
+5V_U725_DPOS: Cd725d.1, RD725d.1, U725.14
+5V_U1284: CD3.1, RD3.1, U1284.10
+5V_UPLDA: CD8.1, RD8.1, UPLDA.24
+5V_UPLDB: CD9.1, RD9.1, UPLDB.24
+5V_UPLDV: CD12.1, RD12.1, UPLDV.24
+5V_UPLDX: CD10.1, RD10.1, UPLDX.24
+5V_UPLDY: CD11.1, RD11.1, UPLDY.24
AD725_BIN: CinB.2, U725.8
AD725_GIN: CinG.2, U725.7
AD725_RIN: CinR.2, U725.6
ASUM0: Ra2r0.2, Rar0.1, Raterm.1
ASUM1: Ra2r1.2, Rar0.2, Rar1.1
ASUM2: Ra2r2.2, Rar1.2, Rar2.1
ASUM3: Ra2r3.2, Rar2.2, Rar3.1
ASUM4: Ra2r4.2, Rar3.2, Rar4.1
ASUM5: Ra2r5.2, Rar4.2, Rar5.1
ASUM6: Ra2r6.2, Rar5.2, Rar6.1
AUD0: Ra2r0.1, U328.14
AUD1: Ra2r1.1, U328.15
AUD2: Ra2r2.1, U328.16
AUD3: Ra2r3.1, U328.17
AUD4: Ra2r4.1, U328.18
AUD5: Ra2r5.1, U328.19
AUD6: Ra2r6.1, U328.23
AUD7: Ra2r7.1, U328.24
AUDIO_OUT: Caud.2, J8.1
AUDIO_SUM: Caud.1, Ra2r7.2, Rar6.2, Raud.1
BEAM_LB_A5: U7D.6, U7E.6, U7F.6, UPLDX.16, UPLDY.3
BEAM_Y0: U7D.3, U7E.3, U7F.3, UPLDX.15, UPLDY.2
BEAM_Y2: U7D.10, U7E.10, U7F.10, UPLDX.17, UPLDY.4
BEAM_Y3: U7D.13, U7E.13, U7F.13, UPLDX.18, UPLDY.5
BEAM_Y4: UPLDX.19, UPLDY.6
BEAM_Y5: UPLDX.20, UPLDY.7
BEAM_Y6: UPLDX.21, UPLDY.8
BEAM_Y7: UPLDX.22, UPLDY.9
CART_A0: J36.4, U1.9, U3.10, UPLDA.2
CART_A1: J36.5, U1.10, U3.9, UPLDA.3
CART_A2: J36.6, U1.11, U3.8, UPLDA.4
CART_A7: J36.11, U1.16, U3.3, UPLDA.9
CART_A8: J36.12, U1.17, U3.25
CART_A9: J36.13, U1.18, U3.24
CART_A10: J36.14, U1.19, U3.21
CART_A14: J36.31, UPLDV.15
CART_A15: J36.32, UPLDV.16
CART_A16: J36.33, UPLDV.17
CART_A17: J36.34, UPLDV.18
CART_A18: J36.35, UPLDV.19
CART_D0: J36.22, Rcd0.2
CART_D0_MCU: Rcd0.1, U20C.18
CART_D1: J36.23, Rcd1.2
CART_D1_MCU: Rcd1.1, U20C.17
CART_D2: J36.24, Rcd2.2
CART_D2_MCU: Rcd2.1, U20C.16
CART_D3: J36.25, Rcd3.2
CART_D3_MCU: Rcd3.1, U20C.15
CART_D4: J36.26, Rcd4.2
CART_D4_MCU: Rcd4.1, U20C.14
CART_D5: J36.27, Rcd5.2
CART_D5_MCU: Rcd5.1, U20C.13
CART_D6: J36.28, Rcd6.2
CART_D6_MCU: Rcd6.1, U20C.12
CART_D7: J36.29, Rcd7.2
CART_D7_MCU: Rcd7.1, U20C.11
CART_OE_MCU: Rcoe.1, UPLDB.20
CART_OE_N: J36.30, Rcoe.2
CART_WE_MCU: Rcwe.1, UPLDB.21
CART_WE_N: J36.36, Rcwe.2
COMPOSITE_OUT: J9.1, R75C.2
COMP_RAW: R75C.1, U725.10
CPU_A3: J36.7, U1.12, U3.7, UPLDA.5
CPU_A4: J36.8, U1.13, U3.6, UPLDA.6
CPU_A5: J36.9, U1.14, U3.5, UPLDA.7
CPU_A11: J36.15, U1.20, U3.23
CPU_A12: J36.16, U1.22, U3.2
CPU_A13: J36.17, U1.23, U3.26
CPU_A14: U1.24, U3.1
CPU_A_LO6: J36.10, U1.15, U3.4, UPLDA.8
CPU_BE: U1.36, UPLDA.10
CPU_D3: U1.30, U3.15, U6.15, U7A.13, U7A.14, U20A.5, U20A.15, U20C.5, U328.5, U1284.27, UPLDB.5, UPLDV.11, UPLDX.5, UPLDY.17
CPU_D5: U1.28, U3.17, U6.17, U7B.5, U7B.6, U20A.7, U20A.13, U20C.7, U328.11, U1284.29, UPLDB.7, UPLDX.7, UPLDY.19
CPU_D6: U1.27, U3.18, U6.18, U7B.10, U7B.11, U20A.8, U20A.12, U20C.8, U328.12, U1284.20, UPLDB.8, UPLDX.8, UPLDY.20
CPU_RWB: U1.34, UPLDA.11
CPU_VA0: U1.33, U3.11, U6.11, U7A.2, U7A.3, U20A.2, U20A.18, U20C.2, U328.2, U1284.24, UPLDB.2, UPLDV.8, UPLDX.2, UPLDY.14
CPU_VA2: U1.31, U3.13, U6.13, U7A.10, U7A.11, U20A.4, U20A.16, U20C.4, U328.4, U1284.26, UPLDB.4, UPLDV.10, UPLDX.4, UPLDY.16
CPU_VA4: U1.29, U3.16, U6.16, U7B.2, U7B.3, U20A.6, U20A.14, U20C.6, U328.6, U1284.28, UPLDB.6, UPLDV.21, UPLDX.6, UPLDY.18
CPU_VA10: U7C.10, U7C.11, UPLDB.13
CPU_VA11: U7C.13, U7C.14, U20A.1, UPLDB.14
CSYNC: J2.4, U725.16, UPLDV.14
DIR_CART245: U20C.1, UPLDB.18
DIR_VID245: U6.26, U20B.1, UPLDB.16
DOT_CLK: Rdot.2, UPLDX.1
DOT_SRC: Rdot.1, Y2.5
FSC4: U725.3, Y3.5
GND: CD1.2, CD2.2, CD3.2, CD4.2, CD5.2, CD6.2, CD7.2, CD8.2, CD9.2, CD10.2, CD11.2, CD12.2, CD13.2, CD14.2, CD15.2, CD16.2, CD17.2, CD18.2, CD19.2, CD20.2, CD21.2, Cbulk.2, Cpad1.2, Cpad2.2, Cva.2, Cxtal4a.2, Cxtal4b.2, Cxtal5a.2, Cxtal5b.2, J1.2, J1.MP, J2.5, J3.1, J4.1, J5.9, J5.10, J6.9, J6.10, J7.2, J7.4, J8.2, J9.2, J36.1, J36.18, J36.19, R75B.2, R75G.2, R75R.2, RD725ag.2, RD725dg.2, RDytrap.2, Raterm.2, Rscale.2, U1.21, U3.14, U6.14, U7A.8, U7B.8, U7C.8, U7D.8, U7E.8, U7F.8, U20A.10, U20B.10, U20C.10, U24.14, U41.14, U328.8, U1284.11, UPLDA.12, UPLDB.12, UPLDV.12, UPLDX.12, UPLDY.12, Y1.4, Y2.4, Y3.4
GND_U725_AGND: Cd725a.2, RD725ag.1, U725.2
GND_U725_DGND: Cd725d.2, RD725dg.1, U725.13
I2C_SCL: J36.21, Rcscl.2
I2C_SCL_MCU: Rcscl.1, U1284.22
I2C_SDA: J36.3, Rcsda.2
I2C_SDA_MCU: Rcsda.1, U1284.23
IRQ_N: U1.4, UPLDY.22
LB_A0: U7D.4, U41.10
LB_A1: U7D.7, U41.9
LB_A2: U7D.9, U41.8
LB_A3: U7D.12, U41.7
LB_A4: U7E.4, U41.6
LB_A5: U7E.7, U41.5
LB_A6: U7E.9, U41.4
LB_A7: U7E.12, U41.3
LB_A8: U7F.4, U41.25
LB_A9: U7F.7, U41.24
LB_A10: U7F.9, U41.21
LB_A11: U7F.12, U41.23
LB_MUX_AB: U7D.1, U7E.1, U7F.1, U1284.17
LB_MUX_G_N: U7D.15, U7E.15, U7F.15
MCU_LB_A2: J6.3, U7D.11, U7F.11, U1284.3
MCU_LB_A3: J6.4, U7D.14, U7F.14, U1284.4
MCU_LB_A4: J6.5, U7E.2, U41.2, U1284.5
MCU_LB_A6: J6.7, U7E.11, U41.1, U1284.7
MCU_LB_A7: J6.8, U7E.14, U1284.8
MUX_G_N: U7A.15, U7B.15, U7C.15
NMI_N: U1.6, UPLDX.14
OE_CART245: U20C.19, UPLDB.19
P1_COIN: J5.7, U1284.34
P1_DOWN: J5.3, U1284.38
P1_LEFT: J5.2, U1284.39
P1_RIGHT: J5.1, U1284.40
P1_START: J5.8, U1284.33
P1_UP: J5.4, U1284.37
P1_X: J5.5, U1284.36
P1_Y: J5.6, U1284.35
P2_LEFT: J6.2, U7D.5, U7F.5, U1284.2
P2_RIGHT: J6.1, U7D.2, U7F.2, U1284.1
P2_Y: J6.6, U7E.5, U41.26, U1284.6
PAD_DATA: Rdata1.1, Rdata2.1, Rpu1.2, U1284.16
PAD_DATA_P1: J3.2, Rdata1.2
PAD_DATA_P2: J4.2, Rdata2.2
PAD_VCC_P1: Cpad1.1, F2.2, J3.4
PAD_VCC_P2: Cpad2.1, F3.2, J4.4
PHI2_BUF: Rphi.2, U1.37, U2.1, U2.2, U7A.1, U7B.1, U7C.1
PHI2_SRC: Rphi.1, Y1.5
PPU_VA1: U1.32, U3.12, U6.12, U7A.5, U7A.6, U20A.3, U20A.17, U20C.3, U328.3, U1284.25, UPLDB.3, UPLDV.9, UPLDX.3, UPLDY.15
PPU_VA7: U1.26, U3.19, U6.19, U7B.13, U7B.14, U20A.9, U20A.11, U20C.9, U328.13, U1284.21, UPLDB.9, UPLDX.9, UPLDY.21
PPU_VA8: U7C.2, U7C.3, UPLDB.10
PPU_VA9: U7C.5, U7C.6, UPLDB.11
PROM_A0: U24.10, UPLDV.2
PROM_A1: U24.9, UPLDV.3
PROM_A2: U24.8, UPLDV.4
PROM_A3: U24.7, UPLDV.5
PROM_A4: U24.6, UPLDV.6
PROM_A5: U24.5, UPLDV.7
PROM_D0: RB0.1, U24.11
PROM_D1: RB1.1, U24.12
PROM_D2: RG0.1, U24.13
PROM_D3: RG1.1, U24.15
PROM_D4: RG2.1, U24.16
PROM_D5: RR0.1, U24.17
PROM_D6: RR1.1, U24.18
PROM_D7: RR2.1, U24.19
RESET_N: J7.3, U1.40, U2.3, UPLDX.13
SCALE_1X: Rscale.1, SW1.1, UPLDV.13
SEL_FE02: U1284.19, UPLDA.15, UPLDB.23
SEL_FE03: UPLDA.16, UPLDX.11
SEL_FE04: UPLDA.17, UPLDY.23
SEL_FE05: U1284.14, UPLDA.18, UPLDA.19
SEL_FE06: U1284.18, UPLDA.14
SEL_FE10: UPLDA.23, UPLDB.22
SEL_FE92: U1284.15, UPLDA.20, UPLDA.21, UPLDA.22, UPLDV.20
VIDEO_B: CinB.1, J2.3, R75B.1, RB0.2, RB1.2
VIDEO_G: CinG.1, J2.2, R75G.1, RG0.2, RG1.2, RG2.2
VIDEO_R: CinR.1, J2.1, R75R.1, RR0.2, RR1.2, RR2.2
VIN_FUSED: F1.2, FB1.1
VIN_PROT: D1.2, F1.1
VIN_RAW: D1.1, J1.1
VRAM_A0: U6.10, U7A.4
VRAM_A1: U6.9, U7A.7
VRAM_A2: U6.8, U7A.9
VRAM_A3: U6.7, U7A.12
VRAM_A4: U6.6, U7B.4
VRAM_A5: U6.5, U7B.7
VRAM_A6: U6.4, U7B.9
VRAM_A7: U6.3, U7B.12
VRAM_A8: U6.25, U7C.4
VRAM_A9: U6.24, U7C.7
VRAM_A10: U6.21, U7C.9
VRAM_A11: U6.23, U7C.12
VRAM_A12: U6.2, U20A.19, UPLDB.15
VRAM_A14: U6.1, U20B.19, UPLDB.17
XTAL328: Cxtal5a.1, U328.9, Y5.1
XTAL328b: Cxtal5b.1, U328.10, Y5.2
XTAL1284: Cxtal4a.1, U1284.13, Y4.1
XTAL1284b: Cxtal4b.1, U1284.12, Y4.2
YTRAP: Lytrap.1, U725.12
YTRAP_MID: Cytrap.1, Lytrap.2
YTRAP_RET: Cytrap.2, RDytrap.1

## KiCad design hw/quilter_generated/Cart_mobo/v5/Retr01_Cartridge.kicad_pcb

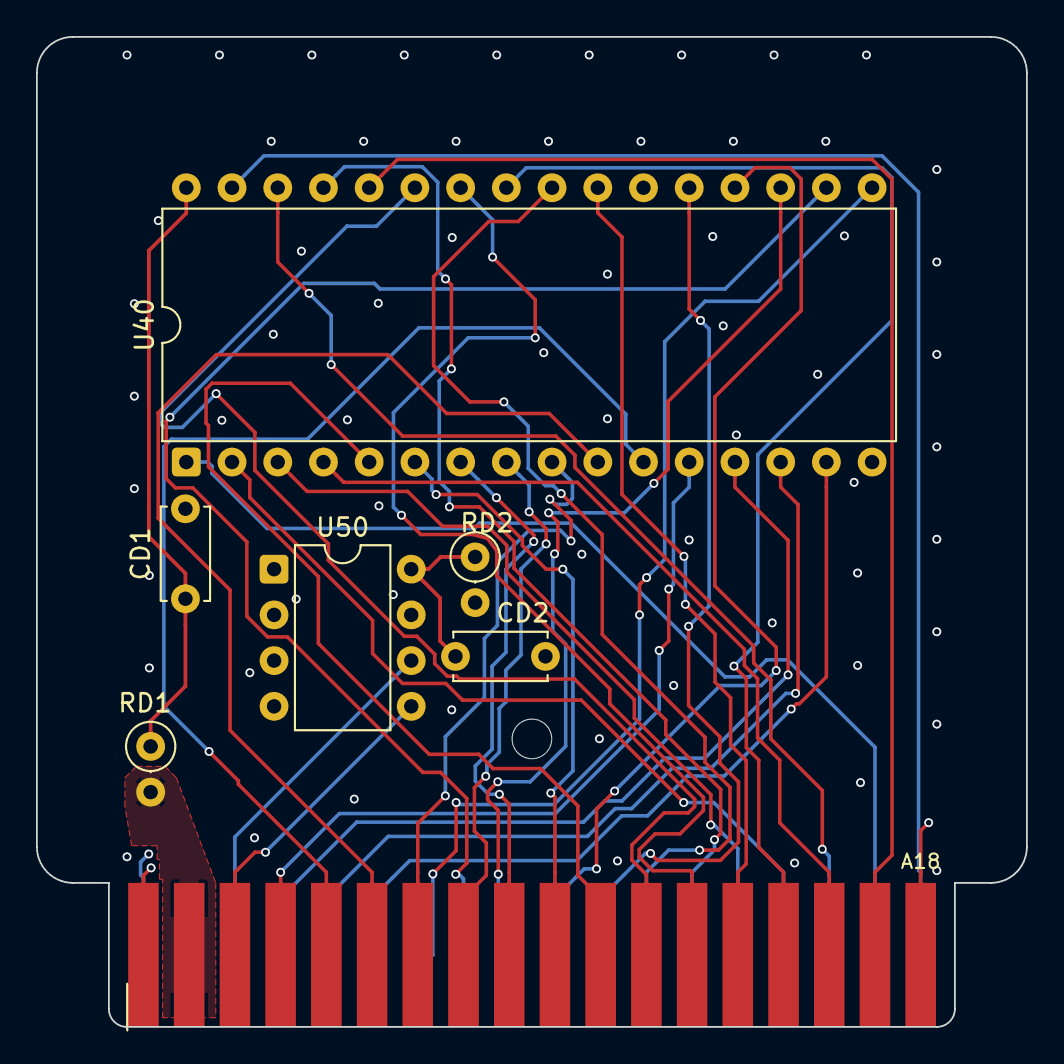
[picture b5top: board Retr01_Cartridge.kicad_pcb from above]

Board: 4 copper layers, 55.0 x 55.0 mm, 8 parts (0 on the bottom side), 35 nets.

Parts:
CD1, CD2: 100nF; C_Disc_D5.0mm_W2.5mm_P5.00mm
J36: CART_EDGE_36; Cart_Edge_2x18_P2.54mm
RD1, RD2: 0; R_Axial_DIN0207_L6.3mm_D2.5mm_P2.54mm_Vertical
Screw: MountingHole_2.2mm_M2
U40: SST39SF040; DIP-32_W15.24mm
U50: 24C64; DIP-8_W7.62mm

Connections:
+5V: J36.2, J36.20, RD1.2, RD2.2
+5V_U40: CD1.1, RD1.1, U40.32
+5V_U50: CD2.1, RD2.1, U50.8
CART_A0: J36.4, U40.12
CART_A1: J36.5, U40.11
CART_A2: J36.6, U40.10
CART_A3: J36.7, U40.9
CART_A4: J36.8, U40.8
CART_A5: J36.9, U40.7
CART_A6: J36.10, U40.6
CART_A7: J36.11, U40.5
CART_A8: J36.12, U40.27
CART_A9: J36.13, U40.26
CART_A10: J36.14, U40.23
CART_A11: J36.15, U40.25
CART_A12: J36.16, U40.4
CART_A13: J36.17, U40.28
CART_A14: J36.31, U40.29
CART_A15: J36.32, U40.3
CART_A16: J36.33, U40.2
CART_A17: J36.34, U40.30
CART_A18: J36.35, U40.1
CART_D0: J36.22, U40.13
CART_D1: J36.23, U40.14
CART_D2: J36.24, U40.15
CART_D3: J36.25, U40.17
CART_D4: J36.26, U40.18
CART_D5: J36.27, U40.19
CART_D6: J36.28, U40.20
CART_D7: J36.29, U40.21
CART_OE_N: J36.30, U40.24
CART_WE_N: J36.36, U40.31
GND: CD1.2, CD2.2, J36.1, J36.18, J36.19, U40.16, U40.22, U50.1, U50.2, U50.3, U50.4, U50.7
I2C_SCL: J36.21, U50.6
I2C_SDA: J36.3, U50.5
